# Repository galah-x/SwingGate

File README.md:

# SwingGate
Controller for an electric remote controlled swing farm gate

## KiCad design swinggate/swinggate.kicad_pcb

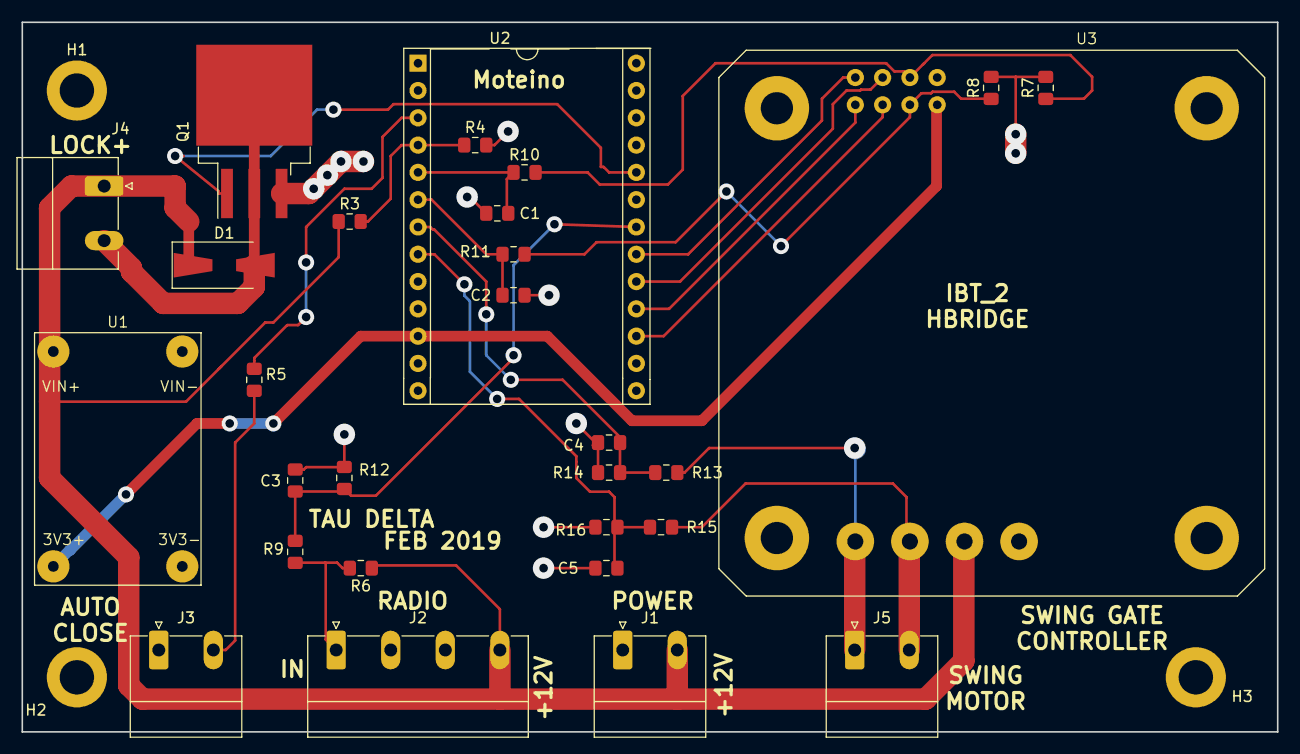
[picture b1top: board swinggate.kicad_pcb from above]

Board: 2 copper layers, 116.8 x 66.0 mm, 32 parts (0 on the bottom side), 22 nets.

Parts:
C1, C2, C3, C4, C5: 100N; C_0805_2012Metric_Pad1.15x1.40mm_HandSolder
D1: APD240VR; D_SMA-SMB_Universal_Handsoldering
H1, H2, H3: MountingHole; MountingHole_3.2mm_M3_DIN965_Pad
J1, J3, J4, J5: Conn_01x02_Female; PhoenixContact_MC_1,5_2-G-5.08_1x02_P5.08mm_Horizontal
J2: Conn_01x04_Female; PhoenixContact_MC_1,5_4-G-5.08_1x04_P5.08mm_Horizontal
Q1: IPB081; TO-263-3_TabPin2
R3: 402K; R_0805_2012Metric_Pad1.15x1.40mm_HandSolder
R4, R9, R10, R11, R13, R15: 100K; R_0805_2012Metric_Pad1.15x1.40mm_HandSolder
R5, R6: 10K; R_0805_2012Metric_Pad1.15x1.40mm_HandSolder
R7, R8: 1K2; R_0805_2012Metric_Pad1.15x1.40mm_HandSolder
R12, R14, R16: 33K; R_0805_2012Metric_Pad1.15x1.40mm_HandSolder
U1: switcher1
U2: Moteino_hcw; DIP-26_W0.8_Socket
U3: IBT2_HBRIDGE; IBT_2

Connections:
+3V3: U1.2, U2.11, U3.7
+12V: D1.1, J1.2, J2.4, J4.1, R3.1, R6.1, U1.1, U3.11
/AUTOCLOSE: R5.1, U2.3
/BATTV_FB: R3.2, R4.1, U2.4
/DRN_L: U2.19, U3.2
/DRN_R: U2.17, U3.1
/IM_FB_L: C1.1, R10.1, U2.5
/IM_FB_R: C2.1, R11.1, U2.6
/IM_L: R7.1, R10.2, U3.6
/IM_R: R8.1, R11.2, U3.5
/ML: J5.1, R13.1, U3.9
/ML_BEMF_FB: C4.1, R13.2, R14.1, U2.7
/MR: J5.2, R15.1, U3.10
/MR_BEMF_FB: C5.1, R15.2, R16.1, U2.8
/PWM_L: U2.18, U3.4
/PWM_R: U2.16, U3.3
/START_N: J2.1, R6.2, R9.2
/START_N_FB: C3.1, R9.1, R12.1, U2.20
/UNLOCK: Q1.1, U2.22
/UNLOCK_N: D1.2, J4.2, Q1.2
GND: C1.2, C2.2, C3.2, C4.2, C5.2, J1.1, J2.2, J2.3, J3.1, Q1.3, R4.2, R7.2, R8.2, R12.2, R14.2, R16.2, U1.3, U1.4, U2.13, U3.8, U3.12
unnamed: J3.2, R5.2

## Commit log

2019-01-27 initial input testing sketch
2019-01-28 basic motor speed control works now
2019-01-28 basic motor speed control. backemf ok, current needs more headroom
2019-01-28 rescaled current wihth 1k2 paralleled.
2019-01-28 and goes backwards too.
2019-02-05 added manual jogging on button
2019-02-05 adjust limits based on front gate
2019-02-05 minor edits
2019-02-05 wait
2019-02-05 run_runtime increases
2019-02-05 ticks reset in wrong place
2019-02-05 speeds in zones
2019-02-10 do a pcb with Kicad
2019-02-11 add radio control and reversing at start/closed to allow lock to release
2019-03-04 initial build onto backgate. backemf was swapped. Not tuned correctly yet.
2019-03-09 variables in ee
2019-03-09 store variables right way around to flash
2019-03-09 add tubner code
2019-03-09 add X to tuner
2019-03-09 tuner is broken
2019-03-09 add more debug
2019-03-10 log to gateway, more time in run_slow, less in missed_limit
2019-03-10 moe tune
2019-03-10 tweak bemf, show drn, to stopped state on stall.
2019-03-16 combine locals
2019-03-16 frontgate installed and somewhat tuned now
2019-03-23 change fast current lim
2019-03-23 choose backgate
2019-03-23 more tuning
2019-03-27 fix sign bug if swing too fast. Also leave autoclose enabled on fast stall open
2020-01-18 start to make direction limits separate adn add proximity switches
2020-01-18 remove eeprom from std build, seems not to work
2020-01-18 adjust limits a bit
2020-02-15 allow to ignore lock pin
2020-04-17 restructure front and back separation, hopefully fix timeout breakage
2020-04-17 change limit message a little
2020-04-18 display ac setting
2020-04-18 change print id
2020-04-18 change buttoned to a bool, re enable button_auto=false if button pressed when not closed.
2020-04-18 dont use pullup input on proximity sw
2020-04-18 reduce open bemf min
2021-04-05 tweak bckgate constants for 16V 4S4P LiPo
2021-10-15 update sch lib
